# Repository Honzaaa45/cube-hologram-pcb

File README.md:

<div align="center">

<picture>
  <source media="(prefers-color-scheme: dark)" srcset="docs/media/banner-dark.svg">
  <source media="(prefers-color-scheme: light)" srcset="docs/media/banner-light.svg">
  
</picture>

# CUBE

**Carte électronique d'un afficheur holographique de bureau — conçue entièrement par du code, vérifiée automatiquement.**

</div>

---

## Aperçu

Le circuit imprimé, rendu depuis les fichiers de ce dépôt. Fond transparent : lisible en thème clair comme en thème sombre.

<div align="center">

</div>

> [!NOTE]
> **La carte n'a pas encore été fabriquée.** Les images ci-dessus sont des rendus 3D produits par KiCad
> à partir des fichiers du dépôt, pas des photos. L'emplacement `docs/media/demo.gif` est réservé pour
> la démonstration du prototype physique — voir [ce qu'il reste à faire](#état-davancement).

## Pourquoi ce projet

Les afficheurs « holographiques » DIY qu'on trouve en ligne se ressemblent tous : un ESP32, un petit écran
OLED monochrome et une breadboard. Le résultat est saccadé, minuscule, et l'électronique est visible.
Ce projet répond à la même envie mais en produit final : image couleur fluide, électronique intégrée sur
une carte sur mesure, et surtout une conception **vérifiable** plutôt que dessinée à la main.

## Le principe optique

L'illusion s'appelle *Pepper's Ghost*. Une dalle posée à plat éclaire un cube séparateur de faisceau ;
la lame à 45° à l'intérieur du cube renvoie l'image vers l'observateur, qui la voit flotter dans le verre.

**La conséquence, et c'est tout le projet :** en Pepper's Ghost, **le noir de l'image est la transparence**.
Un écran LCD, dont le noir est gris, ferait flotter un rectangle lumineux autour du sujet. Un pixel AMOLED
éteint n'émet rien, donc disparaît vraiment. Ce constat commande l'ensemble des choix matériels.

## Architecture

Ce dépôt n'est pas un projet KiCad : c'est une **chaîne de génération** dont KiCad est la sortie.
`design.py` est la seule source de vérité ; tout le reste en découle et se recalcule.

```mermaid
flowchart TD
    D["design.py<br/>source unique de vérité<br/>63 composants · 46 nets · 223 connexions"]

    D --> GS["gen_sch.py"]
    D --> PL["place.py<br/>solveur de placement"]
    D --> GD["gen_docs.py"]

    PL --> RT["router.py<br/>labyrinthe Dijkstra + couture des plans"]
    RT --> CL["cleanup.py<br/>passe de finition"]
    CL --> RJ["routes.json"]
    RJ --> GP["gen_pcb.py"]
    D --> GP

    GS --> SCH["cube.kicad_sch"]
    GP --> PCB["cube.kicad_pcb"]
    PCB --> FZ["fill_zones.py<br/>remplissage des plans"]

    SCH --> V["validate.py + check_cad.py"]
    FZ --> V
    V --> OK{{"ERC 0 erreur<br/>DRC 0 violation<br/>parité 0 écart"}}

    FZ --> GF["gen_fab.py"]
    GF --> FAB["gerbers · CPL · STEP · rendus"]
    GD --> DOC["docs/CARTE.md"]

    OK -.->|"rejoué à chaque push"| CI["GitHub Actions"]
```

<details>
<summary><b>Architecture matérielle de la carte</b> (cliquer pour dérouler)</summary>

```mermaid
flowchart LR
    USB["USB-C<br/>5 V"] --> F["Fusible PPTC<br/>+ ESD USBLC6"]
    F --> BK["AP63203WU<br/>buck 2 A → 3,3 V"]
    BK --> MCU
    F -.->|"USB natif D+/D−"| MCU

    MCU["ESP32-S3-WROOM-1U<br/>N16R8<br/>16 MB flash · 8 MB PSRAM octale"]

    MCU -->|"QSPI + TE"| LCD["J2 — dalle AMOLED<br/>JST-SH 14 pts"]
    MCU -->|"SDIO 4 bits"| SD["microSD"]
    MCU -->|"I2S"| FB["Ferrite"] --> AMP["MAX98357A"] --> SPK["Haut-parleur"]
    MCU -->|"I2C"| TOF["VL53L1X<br/>0x29"]
    MCU -->|"I2C"| ACC["LIS3DH<br/>0x18"]
    MCU -->|"UART0 + BOOT/EN"| DBG["J6 — debug"]
```

</details>

## Démarrage rapide

Il faut **Python 3.9+** et **KiCad 9** installé : les scripts lisent ses bibliothèques officielles de
symboles et d'empreintes. Aucune dépendance Python à installer pour la vérification.

```bash
git clone https://github.com/Honzaaa45/cube-hologram-pcb.git
```

```bash
cd cube-hologram-pcb
```

Vérifier que la conception est cohérente (14 contrôles, ~2 s) :

```bash
python tools/validate.py
```

Rejouer l'ERC, le DRC et le contrôle de parité schéma/PCB :

```bash
python tools/check_cad.py
```

Ouvrir le projet dans KiCad :

```bash
kicad hw/cube.kicad_pro
```

<details>
<summary><b>Régénérer toute la CAO depuis <code>design.py</code></b></summary>

Le schéma et le PCB sont des **sorties**. Après avoir modifié `tools/design.py` :

```bash
python tools/gen_project.py
```

```bash
python tools/gen_sch.py
```

```bash
python tools/gen_pcb.py
```

Si le placement a changé, relancer le solveur puis le routeur (≈ 8 min) :

```bash
python tools/place.py
```

```bash
python tools/router.py
```

Puis remplir les plans de cuivre. **Cette étape n'est pas optionnelle** : sans elle, le DRC voit les
zones vides et signale à tort toutes les pastilles de masse comme non connectées.

```bash
"C:\Program Files\KiCad\9.0\bin\python.exe" tools/fill_zones.py
```

Enfin, produire les fichiers de fabrication :

```bash
python tools/gen_fab.py
```

Si KiCad n'est pas détecté automatiquement, renseignez `KICAD_SHARE` et `KICAD_CLI` — voir
[`.env.example`](.env.example).

</details>

## La carte en bref

| | |
|---|---|
| Microcontrôleur | ESP32-S3-WROOM-1U-N16R8 — 16 MB flash, **8 MB PSRAM octale**, antenne U.FL |
| Écran | connecteur QSPI générique 14 points (JST-SH 1,0 mm), **broche TE câblée** |
| Stockage | microSD en SDIO 4 bits |
| Audio | MAX98357A, ampli classe D I2S mono |
| Capteurs | VL53L1X (temps de vol) + LIS3DH (accéléromètre) |
| Alimentation | USB-C 5 V → AP63203WU, buck 2 A sortie 3,3 V fixe |
| Circuit imprimé | **48 × 52 mm**, 4 couches, 63 composants, montage sur une seule face |
| Empilage | F.Cu / plan de masse / plan +3V3 / B.Cu |

Le détail complet — table des GPIO, brochages des connecteurs, bilan de consommation, cotes pour
Fusion 360 et nomenclature — est dans **[`docs/CARTE.md`](docs/CARTE.md)**.

## Stack et arborescence

**Python 3** (bibliothèque standard uniquement pour la génération) · **KiCad 9** (bibliothèques et
`kicad-cli`) · **ruff** pour le lint · **GitHub Actions** pour la vérification continue.

```
tools/                  chaîne de génération — aucune dépendance externe
  design.py               SOURCE UNIQUE DE VÉRITÉ : composants, netlist, placement
  sexpr.py                lecteur/écrivain de S-expressions KiCad, écrit à la main
  symlib.py               accès aux bibliothèques officielles KiCad 9
  fputil.py               géométrie des empreintes (courtoisie, pastilles, rotation)
  kicadpath.py            localise KiCad sans chemin codé en dur
  place.py                solveur de placement par relaxation sous contraintes
  router.py               routeur labyrinthe (Dijkstra 8 directions) + couture des plans
  cleanup.py              passe de finition sur les liaisons restantes
  import_routes.py        recapture dans routes.json le routage fait a la main
  gen_sch.py              produit hw/cube.kicad_sch
  gen_pcb.py              produit hw/cube.kicad_pcb
  gen_project.py          produit le projet KiCad et les tables de bibliothèques
  fill_zones.py           remplit les plans avec le moteur officiel de KiCad
  gen_fab.py              gerbers, perçage, CPL, STEP, rendus, PDF
  gen_docs.py             produit docs/CARTE.md
  gen_social.py           produit l'aperçu social
  validate.py             14 contrôles de cohérence  ← lancé par la CI
  check_cad.py            verrou de non-régression ERC/DRC  ← lancé par la CI

hw/                     projet KiCad 9 (fichiers générés, mais versionnés)
  cube.kicad_pro          projet : classes de nets, règles de conception
  cube.kicad_sch          schéma, feuille A2, 7 blocs
  cube.kicad_pcb          circuit imprimé 4 couches, plans remplis
  cube.kicad_sym          symbole maison : lecteur microSD Molex 104031-0811
  routes.json             pistes et vias produits par le routeur
  erc.rpt / drc.rpt       rapports de vérification, régénérables
  fab/                    sorties prêtes à commander (gerbers, CPL, STEP, PDF)

docs/
  CARTE.md                fiche technique complète
  media/                  bannières animées, rendus, aperçu social
```

## Décisions techniques

Cinq choix qui expliquent la carte. Pour chacun : la raison, et ce qui a été écarté.

<details open>
<summary><b>1. AMOLED plutôt qu'un IPS SPI</b></summary>

En Pepper's Ghost, le noir affiché **est** la transparence. Le noir d'un LCD est un gris à environ
1000:1 de contraste : le spectateur verrait un rectangle lumineux flotter autour du sujet, et
l'illusion s'effondre. Un pixel AMOLED éteint n'émet rien.

*Écarté :* un IPS SPI (ST7789 ou GC9A01), deux à trois fois moins cher et bien plus documenté. Aucun
gain de fluidité ni de résolution ne compense un fond visible.
</details>

<details>
<summary><b>2. Module WROOM-1U plutôt que le MINI-1, réputé plus petit</b></summary>

Mesures faites avant de trancher : WROOM-1U = 18,0 × 19,2 mm (346 mm²), MINI-1 = 15,4 × 20,5 mm
(316 mm²). Le MINI-1 n'est que **9 % plus petit en surface** — et il est 1,3 mm **plus long**. En
échange on perdrait la PSRAM octale, donc la moitié de la bande passante disponible pour un
framebuffer. De toute façon, ce n'est pas le module qui dimensionne la carte : ce sont l'USB-C, le
connecteur écran et les trous de fixation.

*Écarté :* ESP32-S3-MINI-1-N8 (8 MB flash, aucune PSRAM) et la puce nue ESP32-S3FH4R2 (49 mm², mais
elle impose design RF, quartz, antenne accordée et recertification).
</details>

<details>
<summary><b>3. Un convertisseur à découpage, pas un régulateur linéaire</b></summary>

Bilan en pointe du rail 3,3 V : ESP32-S3 en émission WiFi (355 mA) + dalle AMOLED plein blanc
(~250 mA) + écriture microSD (~100 mA) ≈ 900 mA. Un LDO 5 V → 3,3 V y dissiperait environ 1 W —
dans un boîtier fermé et opaque, à côté d'un capteur de distance.

*Écarté :* un LDO 1 A type AP7361C, plus simple (trois composants au lieu de six) et sans bruit de
découpage. Le calcul thermique tranche.
</details>

<details>
<summary><b>4. L'amplificateur audio alimenté en 3,3 V, pas en 5 V</b></summary>

Le MAX98357A accepte 2,5 à 5,5 V, et 5 V donnerait plus de puissance acoustique. Mais ses seuils
logiques se réfèrent à son alimentation : piloter en 3,3 V une puce alimentée en 5 V place les
niveaux I2S dans une zone non garantie. La carte l'alimente donc en 3,3 V, derrière une perle de
ferrite qui isole son rail de celui du microcontrôleur.

*Écarté :* 5 V avec un adaptateur de niveau (composant et surface en plus, pour une puissance dont un
objet de bureau n'a pas l'usage).
</details>

<details>
<summary><b>5. Une CAO générée par code plutôt que dessinée à la main</b></summary>

C'est le choix structurant du dépôt. `design.py` décrit l'intention ; les scripts produisent le
schéma et le circuit imprimé ; puis un script **compare la netlist réellement exportée par KiCad à
cette intention, connexion par connexion** — 223 sur 223, zéro divergence. La CI rejoue l'ERC, le DRC
et le contrôle de parité à chaque push.

Le bénéfice n'est pas la vitesse : dessiner à la main aurait été plus rapide au départ. C'est de
pouvoir **prouver** que le schéma est juste, et de tout régénérer après un changement sans reprendre
le travail. C'est aussi ce qui a permis de détecter, pendant le développement, que la table des GPIO
documentait `LCD_SCK` là où le netlist portait `LCD_SCK_MCU` — une résistance série séparait les deux.

*Écarté :* KiCad en interactif, l'approche normale et parfaitement légitime. Elle ne donne aucun
moyen de démontrer la cohérence, ni de rejouer la conception.
</details>

## État d'avancement

**Fait et vérifié :**

| Contrôle | Résultat |
|---|---|
| ERC du schéma | **0 erreur** (1 avertissement connu, documenté ci-dessous) |
| Netlist exportée comparée à l'intention | **223 / 223 connexions, 0 divergence** |
| Parité schéma ↔ PCB, vérifiée par KiCad | **0 écart** |
| Placement (contours de courtoisie) | **0 chevauchement**, toutes les pastilles sur la carte |
| DRC du circuit imprimé | **0 violation** |
| Routage | **223 / 223 connexions** |
| Sorties de fabrication | gerbers 4 couches, perçage, CPL, STEP, rendus, PDF |

L'unique avertissement ERC : le pad thermique du MAX98357A est typé « Unspecified » dans la
bibliothèque KiCad officielle et relié à GND. Le comportement est correct, c'est le typage amont qui
est imprécis.

**Intégration continue :** le workflow [`.github/workflows/ci.yml`](.github/workflows/ci.yml) rejoue à
chaque push le lint, la validation de la netlist, puis l'ERC, le DRC et le contrôle de parité sur une
installation KiCad 9 fraîche. Les commandes qu'il exécute sont exactement `python tools/validate.py`
et `python tools/check_cad.py` : elles se lancent à l'identique en local, et c'est là qu'ont été
obtenus les résultats du tableau ci-dessus.

**Routage terminé.** Les 4 dernières liaisons — autour du LIS3DH, boîtier LGA-16 au pas de 0,5 mm —
ont été tirées à la main dans Pcbnew, puis réinjectées dans `hw/routes.json` par
`tools/import_routes.py` : le routage manuel fait désormais partie du pipeline et survit à une
régénération. Restent 8 avertissements de sérigraphie purement cosmétiques (texte rogné là où il
croise une pastille ou le bord), sans effet fonctionnel.

**Limites connues — à lire avant de vous en servir :**

- ⚠️ **La carte n'a jamais été fabriquée ni testée physiquement.** Tout ce qui est affirmé ici est
  vérifié *en CAO*. Une revue humaine reste indispensable avant de commander.
- Le **firmware n'existe pas** : ce dépôt ne contient que le matériel et sa chaîne de génération.
- Le **boîtier n'est pas modélisé** ; `docs/CARTE.md` fournit les cotes nécessaires pour Fusion 360.
- Le routeur maison ne fait **pas de rip-up local**, seulement un réordonnancement global sur quatre
  passes. C'est ce qui explique les 4 liaisons restantes.
- La chaîne est **testée sous Windows** avec KiCad 9.0.7. La détection de KiCad gère Linux et macOS
  mais n'y a pas été éprouvée ; la CI, elle, tourne bien sous Ubuntu.

## Licences

Deux licences, parce que ce dépôt contient deux natures de travail :

- **Code** (`tools/`, CI, scripts) — [MIT](LICENSE).
- **Matériel** (`hw/`, schéma, circuit imprimé, fichiers de fabrication) —
  [CERN-OHL-S-2.0](LICENSE-HARDWARE), la licence matérielle libre fortement réciproque du CERN : qui
  distribue un produit dérivé de cette carte doit en publier les sources de conception.

## Auteur

**Honza** — [@Honzaaa45](https://github.com/Honzaaa45)
Étudiant en BUT GEII, parcours Automatisme et Informatique Industrielle.

Les contributions sont bienvenues, en particulier sur le routeur : voir
[CONTRIBUTING.md](CONTRIBUTING.md).

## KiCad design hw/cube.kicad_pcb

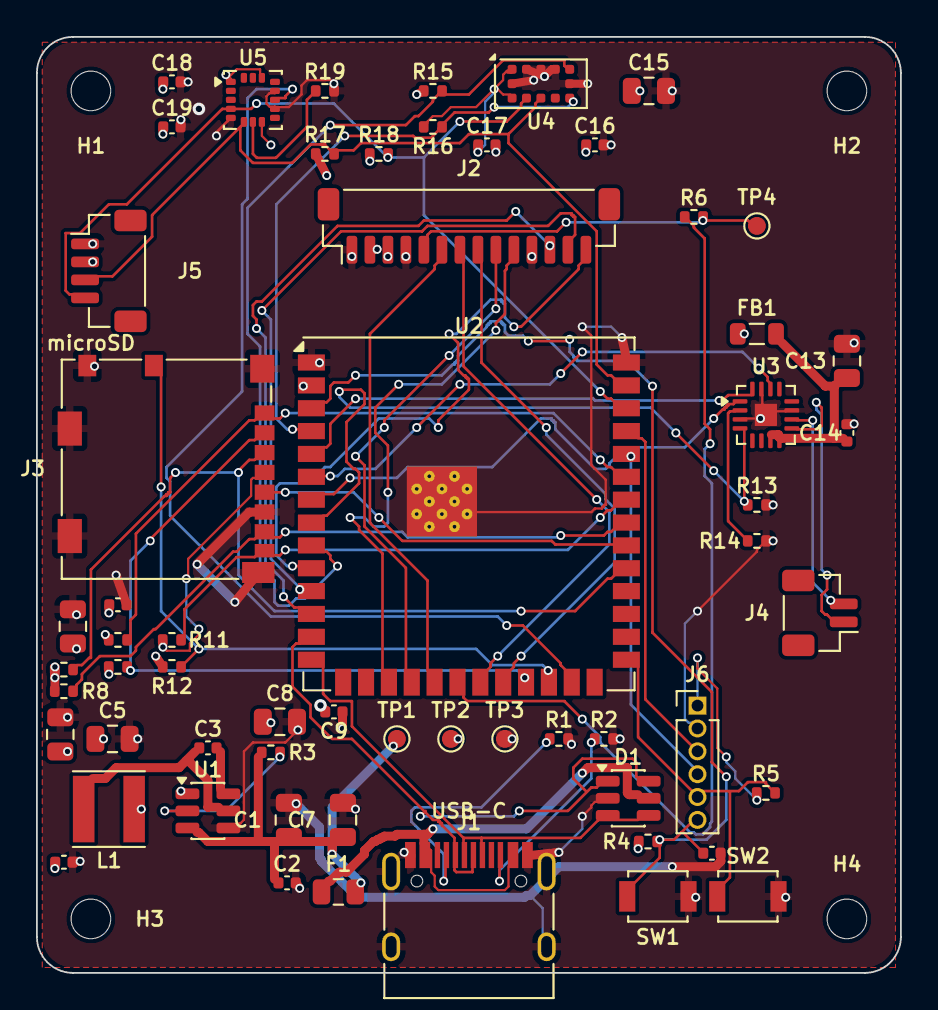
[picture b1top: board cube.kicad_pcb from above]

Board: 4 copper layers, 48.0 x 52.0 mm, 63 parts (0 on the bottom side), 46 nets.

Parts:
C1: 10uF/25V; C_0805_2012Metric
C2, C3, C6, C9, C12, C14, C16, C17, C18, C19: 100nF; C_0402_1005Metric
C4, C5, C7, C8, C13: 22uF/10V; C_0805_2012Metric
C10: 1uF; C_0402_1005Metric
C11, C15: 10uF/10V; C_0805_2012Metric
D1: USBLC6-2SC6; SOT-23-6
F1: 1.1A; Fuse_0805_2012Metric
FB1: 600R@100MHz; L_0805_2012Metric
H1, H2, H3, H4: M2; MountingHole_2.2mm_M2
J1: USB-C; USB_C_Receptacle_HRO_TYPE-C-31-M-12
J2: ECRAN QSPI; JST_SH_BM14B-SRSS-TB_1x14-1MP_P1.00mm_Vertical
J3: microSD; microSD_HC_Molex_104031-0811
J4: HP; JST_SH_BM02B-SRSS-TB_1x02-1MP_P1.00mm_Vertical
J5: I2C EXT; JST_SH_BM04B-SRSS-TB_1x04-1MP_P1.00mm_Vertical
J6: DEBUG; PinHeader_1x06_P1.27mm_Vertical
L1: 2.2uH/3A; L_Taiyo-Yuden_NR-40xx
R1, R2: 5.1k; R_0402_1005Metric
R3, R13: 100k; R_0402_1005Metric
R4, R5, R7, R8, R9, R10, R11, R12, R15, R16: 10k; R_0402_1005Metric
R6, R19: 0R; R_0402_1005Metric
R14: DNP; R_0402_1005Metric
R17, R18: 4.7k; R_0402_1005Metric
SW1: RESET; SW_SPST_B3U-1000P
SW2: BOOT; SW_SPST_B3U-1000P
TP1: +5V; TestPoint_Pad_D1.0mm
TP2: +3V3; TestPoint_Pad_D1.0mm
TP3: GND; TestPoint_Pad_D1.0mm
TP4: LCD_SCK; TestPoint_Pad_D1.0mm
U1: AP63203WU; TSOT-23-6
U2: ESP32-S3-WROOM-1U-N16R8; ESP32-S3-WROOM-1U
U3: MAX98357A; TQFN-16-1EP_3x3mm_P0.5mm_EP1.23x1.23mm
U4: VL53L1X; ST_VL53L1x
U5: LIS3DH; LGA-16_3x3mm_P0.5mm_LayoutBorder3x5y

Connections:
+3V3: C4.1, C5.1, C6.1, C8.1, C9.1, C11.1, C12.1, C15.1, C16.1, C17.1, C18.1, C19.1, FB1.1, J2.2, J2.3, J3.4, J5.2, J6.1, L1.2, R4.1, R5.1, R7.1, R8.1, R9.1, R10.1, R11.1, R12.1, R15.1, R16.1, R17.1, R18.1, TP2.1, U1.1, U2.2, U4.1, U4.11, U5.1, U5.8, U5.14
+5V: C1.1, C2.1, C7.1, F1.2, R3.1, TP1.1, U1.3
/ACC_ADDR: R19.1, U5.7
/ACC_INT1: U2.25, U5.11
/AMP_EN: R13.1, U2.8, U3.4
/AMP_GAIN: R14.1, U3.2
/BOOT: J6.5, R5.2, SW2.1, U2.27
/BST: C3.2, U1.6
/CC1: J1.A5, R1.1
/CC2: J1.B5, R2.1
/EN: C10.1, J6.6, R4.2, SW1.1, U2.3
/I2C_SCL: J5.4, R18.2, U2.38, U4.10, U5.4
/I2C_SDA: J5.3, R17.2, U2.39, U4.9, U5.6
/I2S_BCLK: U2.5, U3.16
/I2S_DOUT: U2.7, U3.1
/I2S_LRCLK: U2.6, U3.14
/LCD_CS: J2.10, U2.17
/LCD_D0: J2.6, U2.19
/LCD_D1: J2.7, U2.21
/LCD_D2: J2.8, U2.22
/LCD_D3: J2.9, U2.18
/LCD_PWR_EN: J2.14, U2.10
/LCD_RST: J2.12, U2.12
/LCD_SCK: J2.5, R6.2, TP4.1
/LCD_SCK_MCU: R6.1, U2.20
/LCD_TE: J2.13, U2.11
/SD_CLK: J3.5, U2.32
/SD_CMD: J3.3, R7.2, U2.31
/SD_D0: J3.7, R8.2, U2.33
/SD_D1: J3.8, R11.2, U2.34
/SD_D2: J3.1, R9.2, U2.35
/SD_D3: J3.2, R10.2, U2.23
/SD_DET: J3.9, R12.2, U2.24
/SPK_N: J4.2, U3.10
/SPK_P: J4.1, U3.9
/SW_NODE: C3.1, L1.1, U1.5
/TOF_INT: R16.2, U2.4, U4.7
/TOF_XSHUT: R15.2, U2.9, U4.5
/UART_RX: J6.4, U2.36
/UART_TX: J6.3, U2.37
/USB_DM: D1.1, D1.6, J1.A7, J1.B7, U2.13
/USB_DP: D1.3, D1.4, J1.A6, J1.B6, U2.14
/VBUS: D1.5, F1.1, J1.A4, J1.A9, J1.B4, J1.B9
/VDD_AMP: C13.1, C14.1, FB1.2, U3.7, U3.8
/VREG_EN: R3.2, U1.2
GND: C1.2, C2.2, C4.2, C5.2, C6.2, C7.2, C8.2, C9.2, C10.2, C11.2, C12.2, C13.2, C14.2, C15.2, C16.2, C17.2, C18.2, C19.2, D1.2, J1.A1, J1.A12, J1.B1, J1.B12, J1.S1, J2.1, J2.4, J2.11, J3.6, J3.10, J3.11, J5.1, J6.2, R1.2, R2.2, R13.2, R14.2, R19.2, SW1.2, SW2.2, TP3.1, U1.4, U2.1, U2.40, U2.41, U3.3, U3.11, U3.15, U3.17, U4.2, U4.3, U4.4, U4.6, U4.12, U5.5, U5.10, U5.12

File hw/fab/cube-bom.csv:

"Reference","Value","Footprint","MPN","Description","QUANTITY"
"C1","10uF/25V","Capacitor_SMD:C_0805_2012Metric","","Decouplage entree buck","1"
"C2,C3,C6,C9,C12,C14,C16-C19","100nF","Capacitor_SMD:C_0402_1005Metric","","Condensateur bootstrap SW->BST,Decouplage AVDDVCSEL,Decouplage HF 3V3 du module,Decouplage HF AVDD ToF,Decouplage HF VDD ampli,Decouplage HF VDD carte SD,Decouplage HF entree buck,Decouplage HF sortie 3.3 V,Decouplage VDD accelero,Decouplage VDD_IO accelero","10"
"C4,C5,C7,C8,C13","22uF/10V","Capacitor_SMD:C_0805_2012Metric","","Reservoir 3V3 du module,Reservoir 5 V,Reservoir VDD ampli,Reservoir sortie 3.3 V","5"
"C10","1uF","Capacitor_SMD:C_0402_1005Metric","","Retard RC sur EN","1"
"C11,C15","10uF/10V","Capacitor_SMD:C_0805_2012Metric","","Reservoir AVDD ToF,Reservoir VDD carte SD","2"
"D1","USBLC6-2SC6","Package_TO_SOT_SMD:SOT-23-6","USBLC6-2SC6","Reseau de protection ESD 2 lignes USB","1"
"F1","1.1A","Fuse:Fuse_0805_2012Metric","MF-MSMF110-2","Fusible reamorcable PPTC, Ihold 1.1 A","1"
"FB1","600R@100MHz","Inductor_SMD:L_0805_2012Metric","BLM21PG600SN1D","Perle de ferrite : isole le rail de l'ampli","1"
"J1","USB-C","Connector_USB:USB_C_Receptacle_HRO_TYPE-C-31-M-12","TYPE-C-31-M-12","Prise USB-C 2.0, 16 pts, montage CMS","1"
"J2","ECRAN QSPI","Connector_JST:JST_SH_BM14B-SRSS-TB_1x14-1MP_P1.00mm_Vertical","BM14B-SRSS-TB","Connecteur ecran AMOLED QSPI, JST-SH 1.0 mm 14 pts","1"
"J3","microSD","Connector_Card:microSD_HC_Molex_104031-0811","104031-0811","Lecteur microSD push-pull avec detection de carte","1"
"J4","HP","Connector_JST:JST_SH_BM02B-SRSS-TB_1x02-1MP_P1.00mm_Vertical","BM02B-SRSS-TB","Sortie haut-parleur 4-8 ohms","1"
"J5","I2C EXT","Connector_JST:JST_SH_BM04B-SRSS-TB_1x04-1MP_P1.00mm_Vertical","BM04B-SRSS-TB","Port I2C deporte (compatible Qwiic/STEMMA-QT)","1"
"J6","DEBUG","Connector_PinHeader_1.27mm:PinHeader_1x06_P1.27mm_Vertical","","UART0 + BOOT + EN (secours si USB natif indisponible)","1"
"L1","2.2uH/3A","Inductor_SMD:L_Taiyo-Yuden_NR-40xx","NR4018T2R2M","Inductance de puissance blindee 4x4 mm","1"
"R1,R2","5.1k","Resistor_SMD:R_0402_1005Metric","","Rd CC1 (role device),Rd CC2 (role device)","2"
"R3,R13","100k","Resistor_SMD:R_0402_1005Metric","","Rappel bas SD_MODE : ampli eteint au boot,Tirage EN du buck vers VIN","2"
"R4,R5,R7-R12,R15,R16","10k","Resistor_SMD:R_0402_1005Metric","","Tirage INT (drain ouvert),Tirage SD_CMD,Tirage SD_D0,Tirage SD_D1,Tirage SD_D2,Tirage SD_D3,Tirage XSHUT,Tirage detection de carte,Tirage haut de EN,Tirage haut de IO0 (BOOT)","10"
"R6,R19","0R","Resistor_SMD:R_0402_1005Metric","","Adresse accelero : 0R vers GND = 0x18, vers +3V3 = 0x19,Serie sur LCD_SCK - monter 22R si sonnerie","2"
"R14","DNP","Resistor_SMD:R_0402_1005Metric","","Selection de gain : vide=9 dB, 100k vers GND=12 dB","1"
"R17,R18","4.7k","Resistor_SMD:R_0402_1005Metric","","Tirage I2C SCL,Tirage I2C SDA","2"
"SW1","RESET","Button_Switch_SMD:SW_SPST_B3U-1000P","B3U-1000P","Bouton RESET (EN vers GND)","1"
"SW2","BOOT","Button_Switch_SMD:SW_SPST_B3U-1000P","B3U-1000P","Bouton BOOT (IO0 vers GND)","1"
"U1","AP63203WU","Package_TO_SOT_SMD:TSOT-23-6","AP63203WU-7","Buck synchrone 2 A, 1.1 MHz, sortie 3.3 V fixe","1"
"U2","ESP32-S3-WROOM-1U-N16R8","RF_Module:ESP32-S3-WROOM-1U","ESP32-S3-WROOM-1U-N16R8","MCU WiFi/BLE, 16 MB flash, 8 MB PSRAM octale, antenne U.FL","1"
"U3","MAX98357A","Package_DFN_QFN:TQFN-16-1EP_3x3mm_P0.5mm_EP1.23x1.23mm","MAX98357AETE+T","Ampli classe D I2S mono 3.2 W","1"
"U4","VL53L1X","Sensor_Distance:ST_VL53L1x","VL53L1CXV0FY/1","Telemetre ToF laser 4 m, I2C 0x29","1"
"U5","LIS3DH","Package_LGA:LGA-16_3x3mm_P0.5mm_LayoutBorder3x5y","LIS3DHTR","Accelerometre 3 axes, I2C 0x18 (SDO=GND)","1"

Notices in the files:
README.md:
Licence matériel : CERN-OHL-S-2.0
